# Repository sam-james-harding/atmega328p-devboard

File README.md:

# atmega328p-devboard

This is my own custom development board, made for the ATmega328P. I created this both as learning experience (in PCB design and in soldering SMD components), and as a practical device to assist in prototyping.

## Features
- USB connection providing power and allowing serial communication
  - Micro-USB B for Rev. 1
  - USB C for Rev. 2
- USB-to-UART functionality via the MCP2221A IC
- Regulated 3.3V supply: power, supplied either through the USB connection or the VIN pin, can be supplied at up to 6V (using the MCP1825 voltage regulator)
- Switches for both power and USB-to-serial functionality
- LEDs to show power status and serial communication
- 16MHz crystal
- Reset button
- 6-pin ISP header (i.e. for AVRISP or the Pololu AVR programmer)

## Images

### Rev. 1

### Rev. 2

## Drawings
- [Schematic](https://github.com/sam-james-harding/atmega328p-devboard/blob/main/rev_1/documents/Schematic.pdf)
- PCB [front](https://github.com/sam-james-harding/atmega328p-devboard/blob/main/rev_1/documents/PCB%20Front.pdf)
and [back](https://github.com/sam-james-harding/atmega328p-devboard/blob/main/rev_1/documents/PCB%20Back.pdf)

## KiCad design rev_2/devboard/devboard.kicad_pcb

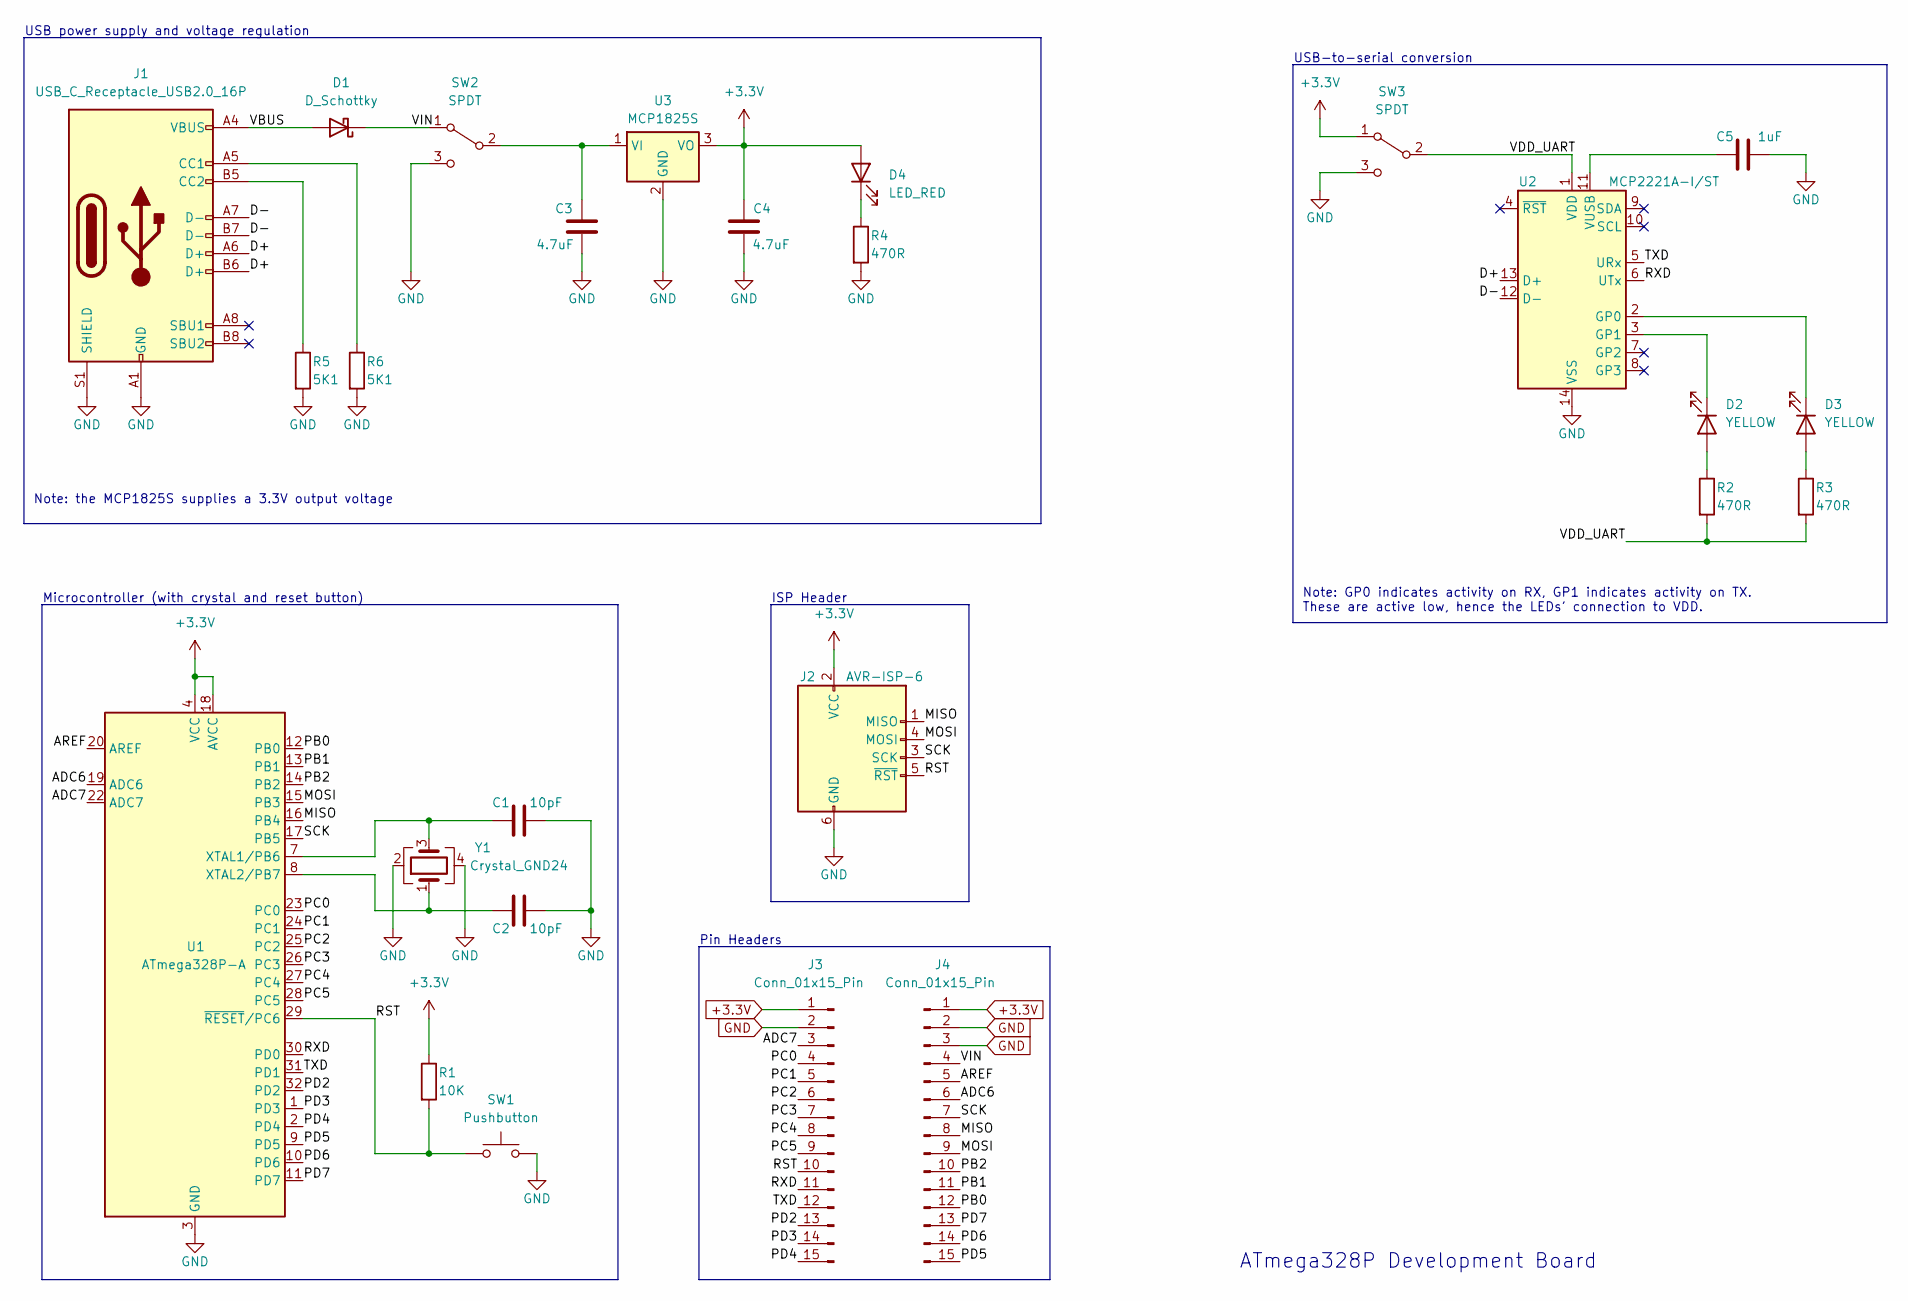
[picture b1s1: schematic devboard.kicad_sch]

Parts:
C1, C2: 10pF; C_0805_2012Metric_Pad1.18x1.45mm_HandSolder
C3, C4: 4.7uF; C_0805_2012Metric_Pad1.18x1.45mm_HandSolder
C5: 1uF; C_0805_2012Metric_Pad1.18x1.45mm_HandSolder; Mfr Part # C0805C105K3RACTU
D1: D_Schottky; D_0805_2012Metric_Pad1.15x1.40mm_HandSolder
D2, D3: YELLOW; LED_0805_2012Metric_Pad1.15x1.40mm_HandSolder
D4: LED_RED; LED_0805_2012Metric_Pad1.15x1.40mm_HandSolder
J1: USB_C_Receptacle_USB2.0_16P; USB_C_Receptacle_GCT_USB4105-xx-A_16P_TopMnt_Horizontal
J2: AVR-ISP-6; PinHeader_2x03_P2.54mm_Vertical
J3, J4: Conn_01x15_Pin; PinHeader_1x15_P2.54mm_Vertical
R1: 10K; R_0805_2012Metric_Pad1.20x1.40mm_HandSolder
R2, R3, R4: 470R; R_0805_2012Metric_Pad1.20x1.40mm_HandSolder
R5, R6: 5K1; R_0805_2012Metric_Pad1.20x1.40mm_HandSolder
SW1: Pushbutton; SW_Push_1P1T_NO_CK_KMR2
SW2, SW3: SPDT; slide_switch
U1: ATmega328P-A; TQFP-32_7x7mm_P0.8mm
U2: MCP2221A-I/ST; TSSOP-14_4.4x5mm_P0.65mm; Mfr Part # MCP2221A-I/ST
U3: MCP1825S; SOT-223-3_TabPin2
Y1: Crystal_GND24; Crystal_SMD_3225-4Pin_3.2x2.5mm_HandSoldering

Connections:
+3.3V: C4.2, D4.2 (A), J2.2 (VCC), J3.1, J4.1, R1.1, SW3.1 (A), U1.4 (VCC), U1.6 (VCC), U1.18 (AVCC), U3.3 (VO)
/ADC6: J4.6, U1.19 (ADC6)
/ADC7: J3.3, U1.22 (ADC7)
/AREF: J4.5, U1.20 (AREF)
/D+: J1.A6 (D+), J1.B6 (D+), U2.13 (D+)
/D-: J1.A7 (D-), J1.B7 (D-), U2.12 (D-)
/MISO: J2.1 (MISO), J4.8, U1.16 (PB4)
/MOSI: J2.4 (MOSI), J4.9, U1.15 (PB3)
/PB0: J4.12, U1.12 (PB0)
/PB1: J4.11, U1.13 (PB1)
/PB2: J4.10, U1.14 (PB2)
/PC0: J3.4, U1.23 (PC0)
/PC1: J3.5, U1.24 (PC1)
/PC2: J3.6, U1.25 (PC2)
/PC3: J3.7, U1.26 (PC3)
/PC4: J3.8, U1.27 (PC4)
/PC5: J3.9, U1.28 (PC5)
/PD2: J3.13, U1.32 (PD2)
/PD3: J3.14, U1.1 (PD3)
/PD4: J3.15, U1.2 (PD4)
/PD5: J4.15, U1.9 (PD5)
/PD6: J4.14, U1.10 (PD6)
/PD7: J4.13, U1.11 (PD7)
/RST: J2.5 (~RST), J3.10, R1.2, SW1.1, U1.29 (~RESET/PC6)
/RXD: J3.11, U1.30 (PD0), U2.6 (UTx)
/SCK: J2.3 (SCK), J4.7, U1.17 (PB5)
/TXD: J3.12, U1.31 (PD1), U2.5 (URx)
/VBUS: D1.2 (A), J1.A4 (VBUS), J1.A9 (VBUS), J1.B4 (VBUS), J1.B9 (VBUS)
/VDD_UART: R2.2, R3.2, SW3.2 (B), U2.1 (VDD)
/VIN: D1.1 (K), J4.4, SW2.1 (A)
GND: C1.1, C2.1, C3.2, C4.1, C5.1, J1.A1 (GND), J1.A12 (GND), J1.B1 (GND), J1.B12 (GND), J1.S1 (SHIELD), J2.6 (GND), J3.2, J4.2, J4.3, R4.2, R5.2, R6.2, SW1.2, SW2.3 (C), SW3.3 (C), U1.3 (GND), U1.5 (GND), U1.21 (GND), U2.14 (VSS), U3.2 (GND), Y1.2, Y1.4
unnamed: D2.2 (A), R2.1
unnamed: D2.1 (K), U2.3 (GP1)
unnamed: D3.2 (A), R3.1
unnamed: D3.1 (K), U2.2 (GP0)
unnamed: D4.1 (K), R4.1
unnamed: J1.A5 (CC1), R6.1
unnamed: J1.B5 (CC2), R5.1
unnamed: C3.1, SW2.2 (B), U3.1 (VI)
unnamed: C1.2, U1.7 (XTAL1/PB6), Y1.3
unnamed: C2.2, U1.8 (XTAL2/PB7), Y1.1
unnamed: C5.2, U2.11 (VUSB)

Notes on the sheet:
ISP Header
Pin Headers
USB-to-serial conversion
ATmega328P Development Board
Note: the MCP1825S supplies a 3.3V output voltage
Microcontroller (with crystal and reset button)
Note: GP0 indicates activity on RX, GP1 indicates activity on TX. These are active low, hence the LEDs' connection to VDD.
USB power supply and voltage regulation

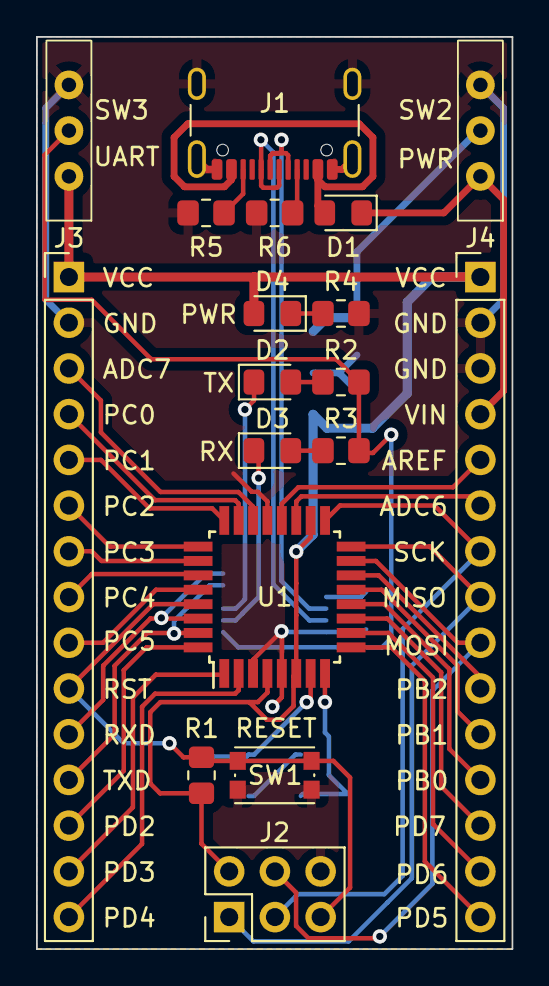
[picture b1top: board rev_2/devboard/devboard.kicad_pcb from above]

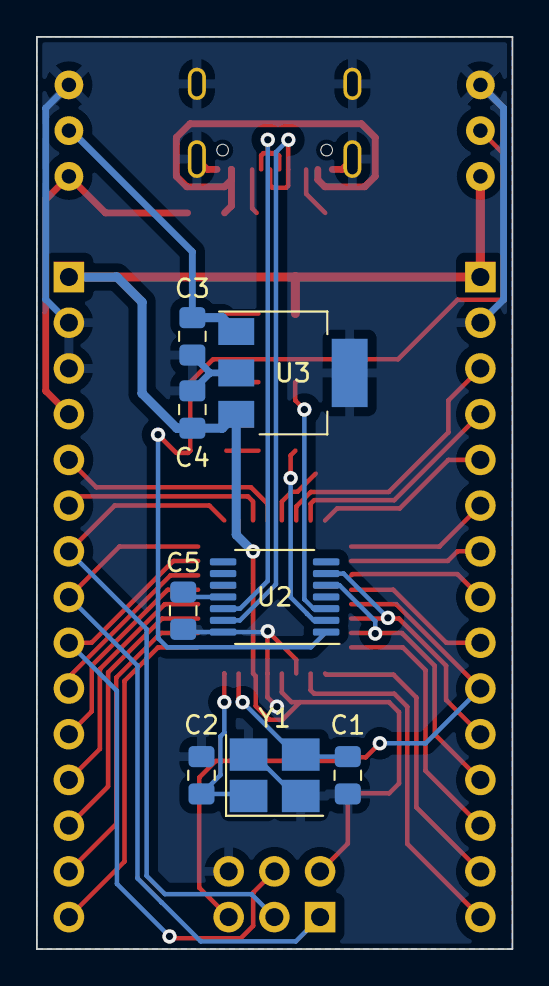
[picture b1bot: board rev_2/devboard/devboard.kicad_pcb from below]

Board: 2 copper layers, 26.4 x 50.7 mm, 26 parts (8 on the bottom side), 42 nets.

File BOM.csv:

Ref,Qnty,Value,Cmp name,Footprint,Description,Manufacturer,Mfr. Part #,Package,Vendor
"C1, C2",2,10pF X7R,C,Capacitor_SMD:C_0805_2012Metric_Pad1.18x1.45mm_HandSolder,Ceramic capacitor,KEMET,C0805C100K3RACTU,0805,Mouser
"C3, C4",2,4.7uF X7R,C,Capacitor_SMD:C_0805_2012Metric_Pad1.18x1.45mm_HandSolder,Ceramic capacitor,KEMET,C0805C475K3PAC7210,0805,Mouser
C5,1,1uF X7R,C,Capacitor_SMD:C_0805_2012Metric_Pad1.18x1.45mm_HandSolder,Ceramic capacitor,KEMET,C0805C105K3RACTU,0805,Mouser
D1,1,,D_Schottky,Diode_SMD:D_0805_2012Metric_Pad1.15x1.40mm_HandSolder,Schottky diode,KYOCERA AVX,SD0805S020S1R0,0805,Mouser
"D2, D3",2,,LED_YLW,LED_SMD:LED_0805_2012Metric_Pad1.15x1.40mm_HandSolder,Light emitting diode,Wurth Elektronik,150080YS75000,0805,Mouser
D4,1,,LED_RED,LED_SMD:LED_0805_2012Metric_Pad1.15x1.40mm_HandSolder,Light emitting diode,Wurth Elektronik,150080SS75000,0805,Mouser
J1,1,,USB_B_Micro,Connector_USB:USB_Micro-B_Amphenol_10118194_Horizontal,USB Micro Type B connector,Amphenol FCI,10118194-0011LF,,Mouser
J2,1,,AVR-ISP-6,Connector_IDC:IDC-Header_2x03_P2.54mm_Vertical,Atmel 6-pin ISP connector,TE Connectivity,1761681-1,,Mouser
"J3, J4",2,,Conn_01x15_Pin,Connector_PinHeader_2.54mm:PinHeader_1x15_P2.54mm_Vertical,"Generic header, single row, 01x15, 2.54mm pitch",Samtec,TSW-115-23-T-S,,Mouser
R1,1,10K 1/4 W,R,Resistor_SMD:R_0805_2012Metric_Pad1.20x1.40mm_HandSolder,Resistor,YAGEO,AC0805FR-7W10KL,0805,Mouser
"R2, R3, R4",3,200R 1/4 W,R,Resistor_SMD:R_0805_2012Metric_Pad1.20x1.40mm_HandSolder,Resistor,YAGEO,RC0805FR-7W200RL,0805,Mouser
SW1,1,,Pushbutton,Button_Switch_THT:SW_PUSH_6mm,"Push button switch, generic, two pins",Apem,ADTS63KV,,Mouser
"SW2, SW3",2,,SPDT,devboard:slide_switch,"Switch, single pole double throw",CUI Devices,MSS-102545-28A-D,,Mouser
U1,1,,ATmega328P-P,Package_DIP:DIP-28_W7.62mm,"20MHz, 32kB Flash, 2kB SRAM, 1kB EEPROM, DIP-28",Microchip,ATMEGA328P-P,DIP-28,Mouser
U2,1,,MCP2221A-I/ST,Package_SO:TSSOP-14_4.4x5mm_P0.65mm,"USB to I2C/UART Protocol Converter with GPIO, TSSOP-14",Microchip,MCP2221A-I/ST,TSSOP-14,Mouser
U3,1,,MCP1825S,Package_TO_SOT_SMD:SOT-223-3_TabPin2,"500mA, Low-Voltage, Low Quiescent Current LDO Regulator",Microchip,MCP1825S,SOT-223-3,Mouser
Y1,1,16MHz,Crystal,Crystal:Crystal_HC49-U_Vertical,Two pin crystal,Vishay/Dale,XT9S20ANA16M ,HC49,Mouser

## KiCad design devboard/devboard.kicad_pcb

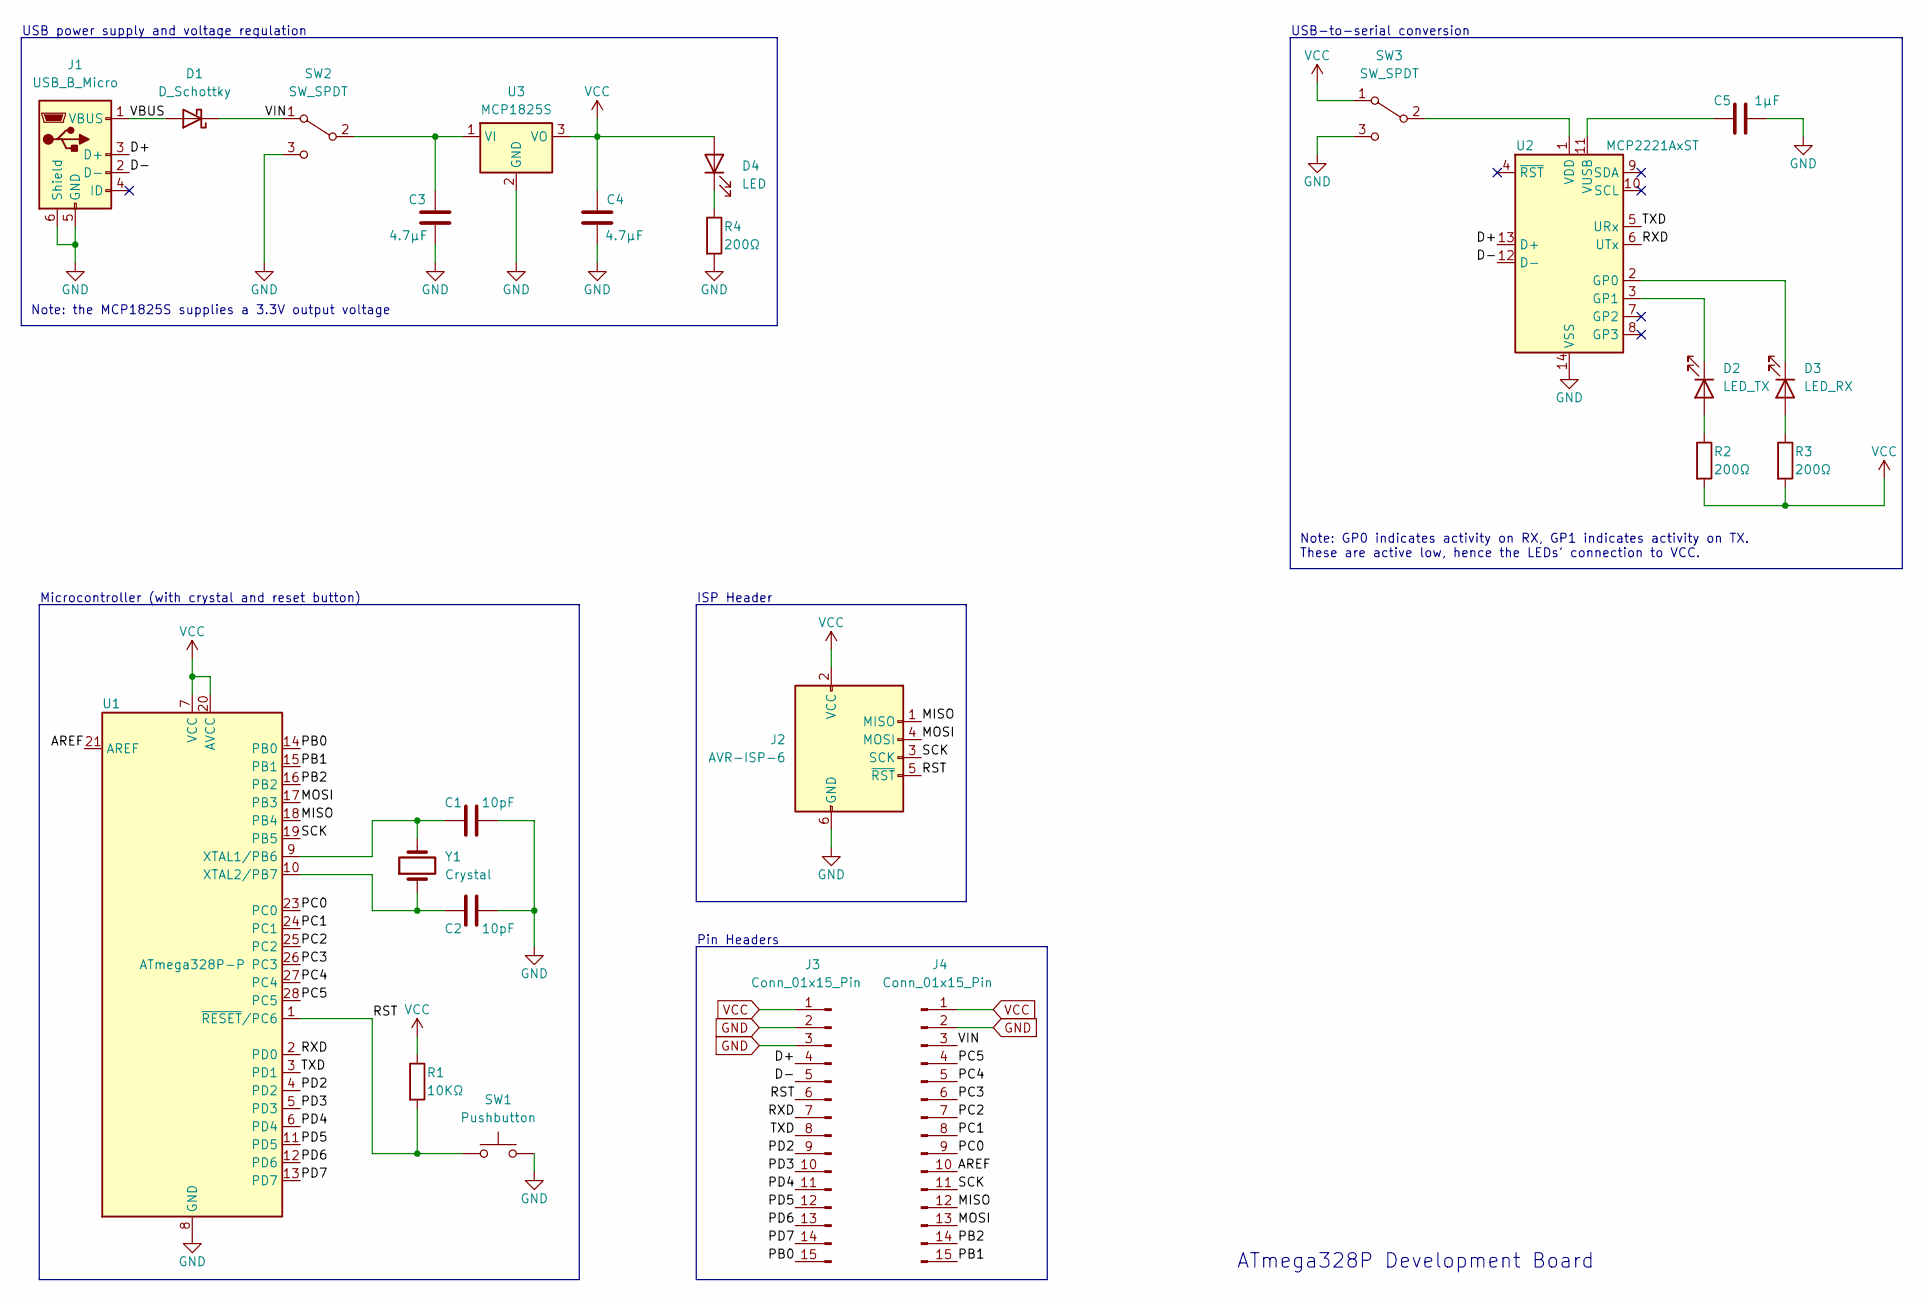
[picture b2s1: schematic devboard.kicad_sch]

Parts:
C1, C2: 10pF; C_0805_2012Metric_Pad1.18x1.45mm_HandSolder
C3, C4: 4.7μF; C_0805_2012Metric_Pad1.18x1.45mm_HandSolder
C5: 1μF; C_0805_2012Metric_Pad1.18x1.45mm_HandSolder
D1: D_Schottky; D_0805_2012Metric_Pad1.15x1.40mm_HandSolder
D2: LED_TX; LED_0805_2012Metric_Pad1.15x1.40mm_HandSolder
D3: LED_RX; LED_0805_2012Metric_Pad1.15x1.40mm_HandSolder
D4: LED; LED_0805_2012Metric_Pad1.15x1.40mm_HandSolder
J1: USB_B_Micro; USB_Micro-B_Amphenol_10118194_Horizontal
J2: AVR-ISP-6; IDC-Header_2x03_P2.54mm_Vertical
J3, J4: Conn_01x15_Pin; PinHeader_1x15_P2.54mm_Vertical
R1: 10KΩ; R_0805_2012Metric_Pad1.20x1.40mm_HandSolder
R2, R3, R4: 200Ω; R_0805_2012Metric_Pad1.20x1.40mm_HandSolder
SW1: Pushbutton; SW_PUSH_6mm
SW2, SW3: SW_SPDT; slide_switch
U1: ATmega328P-P; DIP-28_W7.62mm
U2: MCP2221AxST; TSSOP-14_4.4x5mm_P0.65mm
U3: MCP1825S; SOT-223-3_TabPin2
Y1: Crystal; Crystal_HC49-U_Vertical

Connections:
/AREF: J4.10, U1.21 (AREF)
/D+: J1.3 (D+), J3.4, U2.13 (D+)
/D-: J1.2 (D-), J3.5, U2.12 (D-)
/MISO: J2.1 (MISO), J4.12, U1.18 (PB4)
/MOSI: J2.4 (MOSI), J4.13, U1.17 (PB3)
/PB0: J3.15, U1.14 (PB0)
/PB1: J4.15, U1.15 (PB1)
/PB2: J4.14, U1.16 (PB2)
/PC0: J4.9, U1.23 (PC0)
/PC1: J4.8, U1.24 (PC1)
/PC2: J4.7, U1.25 (PC2)
/PC3: J4.6, U1.26 (PC3)
/PC4: J4.5, U1.27 (PC4)
/PC5: J4.4, U1.28 (PC5)
/PD2: J3.9, U1.4 (PD2)
/PD3: J3.10, U1.5 (PD3)
/PD4: J3.11, U1.6 (PD4)
/PD5: J3.12, U1.11 (PD5)
/PD6: J3.13, U1.12 (PD6)
/PD7: J3.14, U1.13 (PD7)
/RST: J2.5 (~RST), J3.6, R1.2, SW1.1, U1.1 (~RESET/PC6)
/RXD: J3.7, U1.2 (PD0), U2.6 (UTx)
/SCK: J2.3 (SCK), J4.11, U1.19 (PB5)
/TXD: J3.8, U1.3 (PD1), U2.5 (URx)
/VBUS: D1.2 (A), J1.1 (VBUS)
/VIN: D1.1 (K), J4.3, SW2.1 (A)
GND: C1.1, C2.1, C3.2, C4.1, C5.1, J1.5 (GND), J1.6 (Shield), J2.6 (GND), J3.2, J3.3, J4.2, R4.2, SW1.2, SW2.3 (C), SW3.3 (C), U1.8 (GND), U1.22 (GND), U2.14 (VSS), U3.2 (GND)
unnamed: D2.2 (A), R2.1
unnamed: D2.1 (K), U2.3 (GP1)
unnamed: D3.2 (A), R3.1
unnamed: D3.1 (K), U2.2 (GP0)
unnamed: D4.1 (K), R4.1
unnamed: C3.1, SW2.2 (B), U3.1 (VI)
unnamed: SW3.2 (B), U2.1 (VDD)
unnamed: C1.2, U1.9 (XTAL1/PB6), Y1.2
unnamed: C2.2, U1.10 (XTAL2/PB7), Y1.1
unnamed: C5.2, U2.11 (VUSB)
VCC: C4.2, D4.2 (A), J2.2 (VCC), J3.1, J4.1, R1.1, R2.2, R3.2, SW3.1 (A), U1.7 (VCC), U1.20 (AVCC), U3.3 (VO)

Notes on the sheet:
ISP Header
Pin Headers
USB-to-serial conversion
ATmega328P Development Board
Note: the MCP1825S supplies a 3.3V output voltage
Microcontroller (with crystal and reset button)
Note: GP0 indicates activity on RX, GP1 indicates activity on TX. These are active low, hence the LEDs' connection to VCC.
USB power supply and voltage regulation

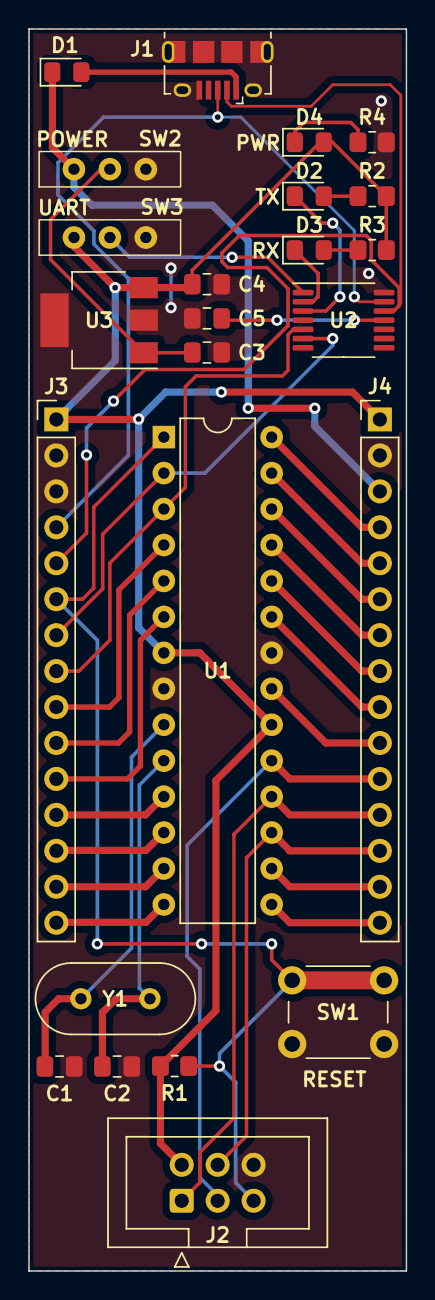
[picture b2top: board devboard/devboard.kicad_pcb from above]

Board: 2 copper layers, 26.7 x 87.8 mm, 24 parts (0 on the bottom side), 38 nets.

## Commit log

2024-01-07 Added CAD files and printouts
2024-01-07 Revert "Added CAD files and printouts"
    This reverts commit 5d408bc1e87f594881d4da881a5795643422694f.
2024-01-07 Removed backups from git
2024-01-11 Minor changes + added BOM
2024-01-24 Added image
2024-02-02 Changed file structure
2024-02-11 Routed most of rev_2
2024-03-18 Finished rev 2
2024-07-21 Added image of rev 2
2024-07-21 Update README.md for rev. 2
